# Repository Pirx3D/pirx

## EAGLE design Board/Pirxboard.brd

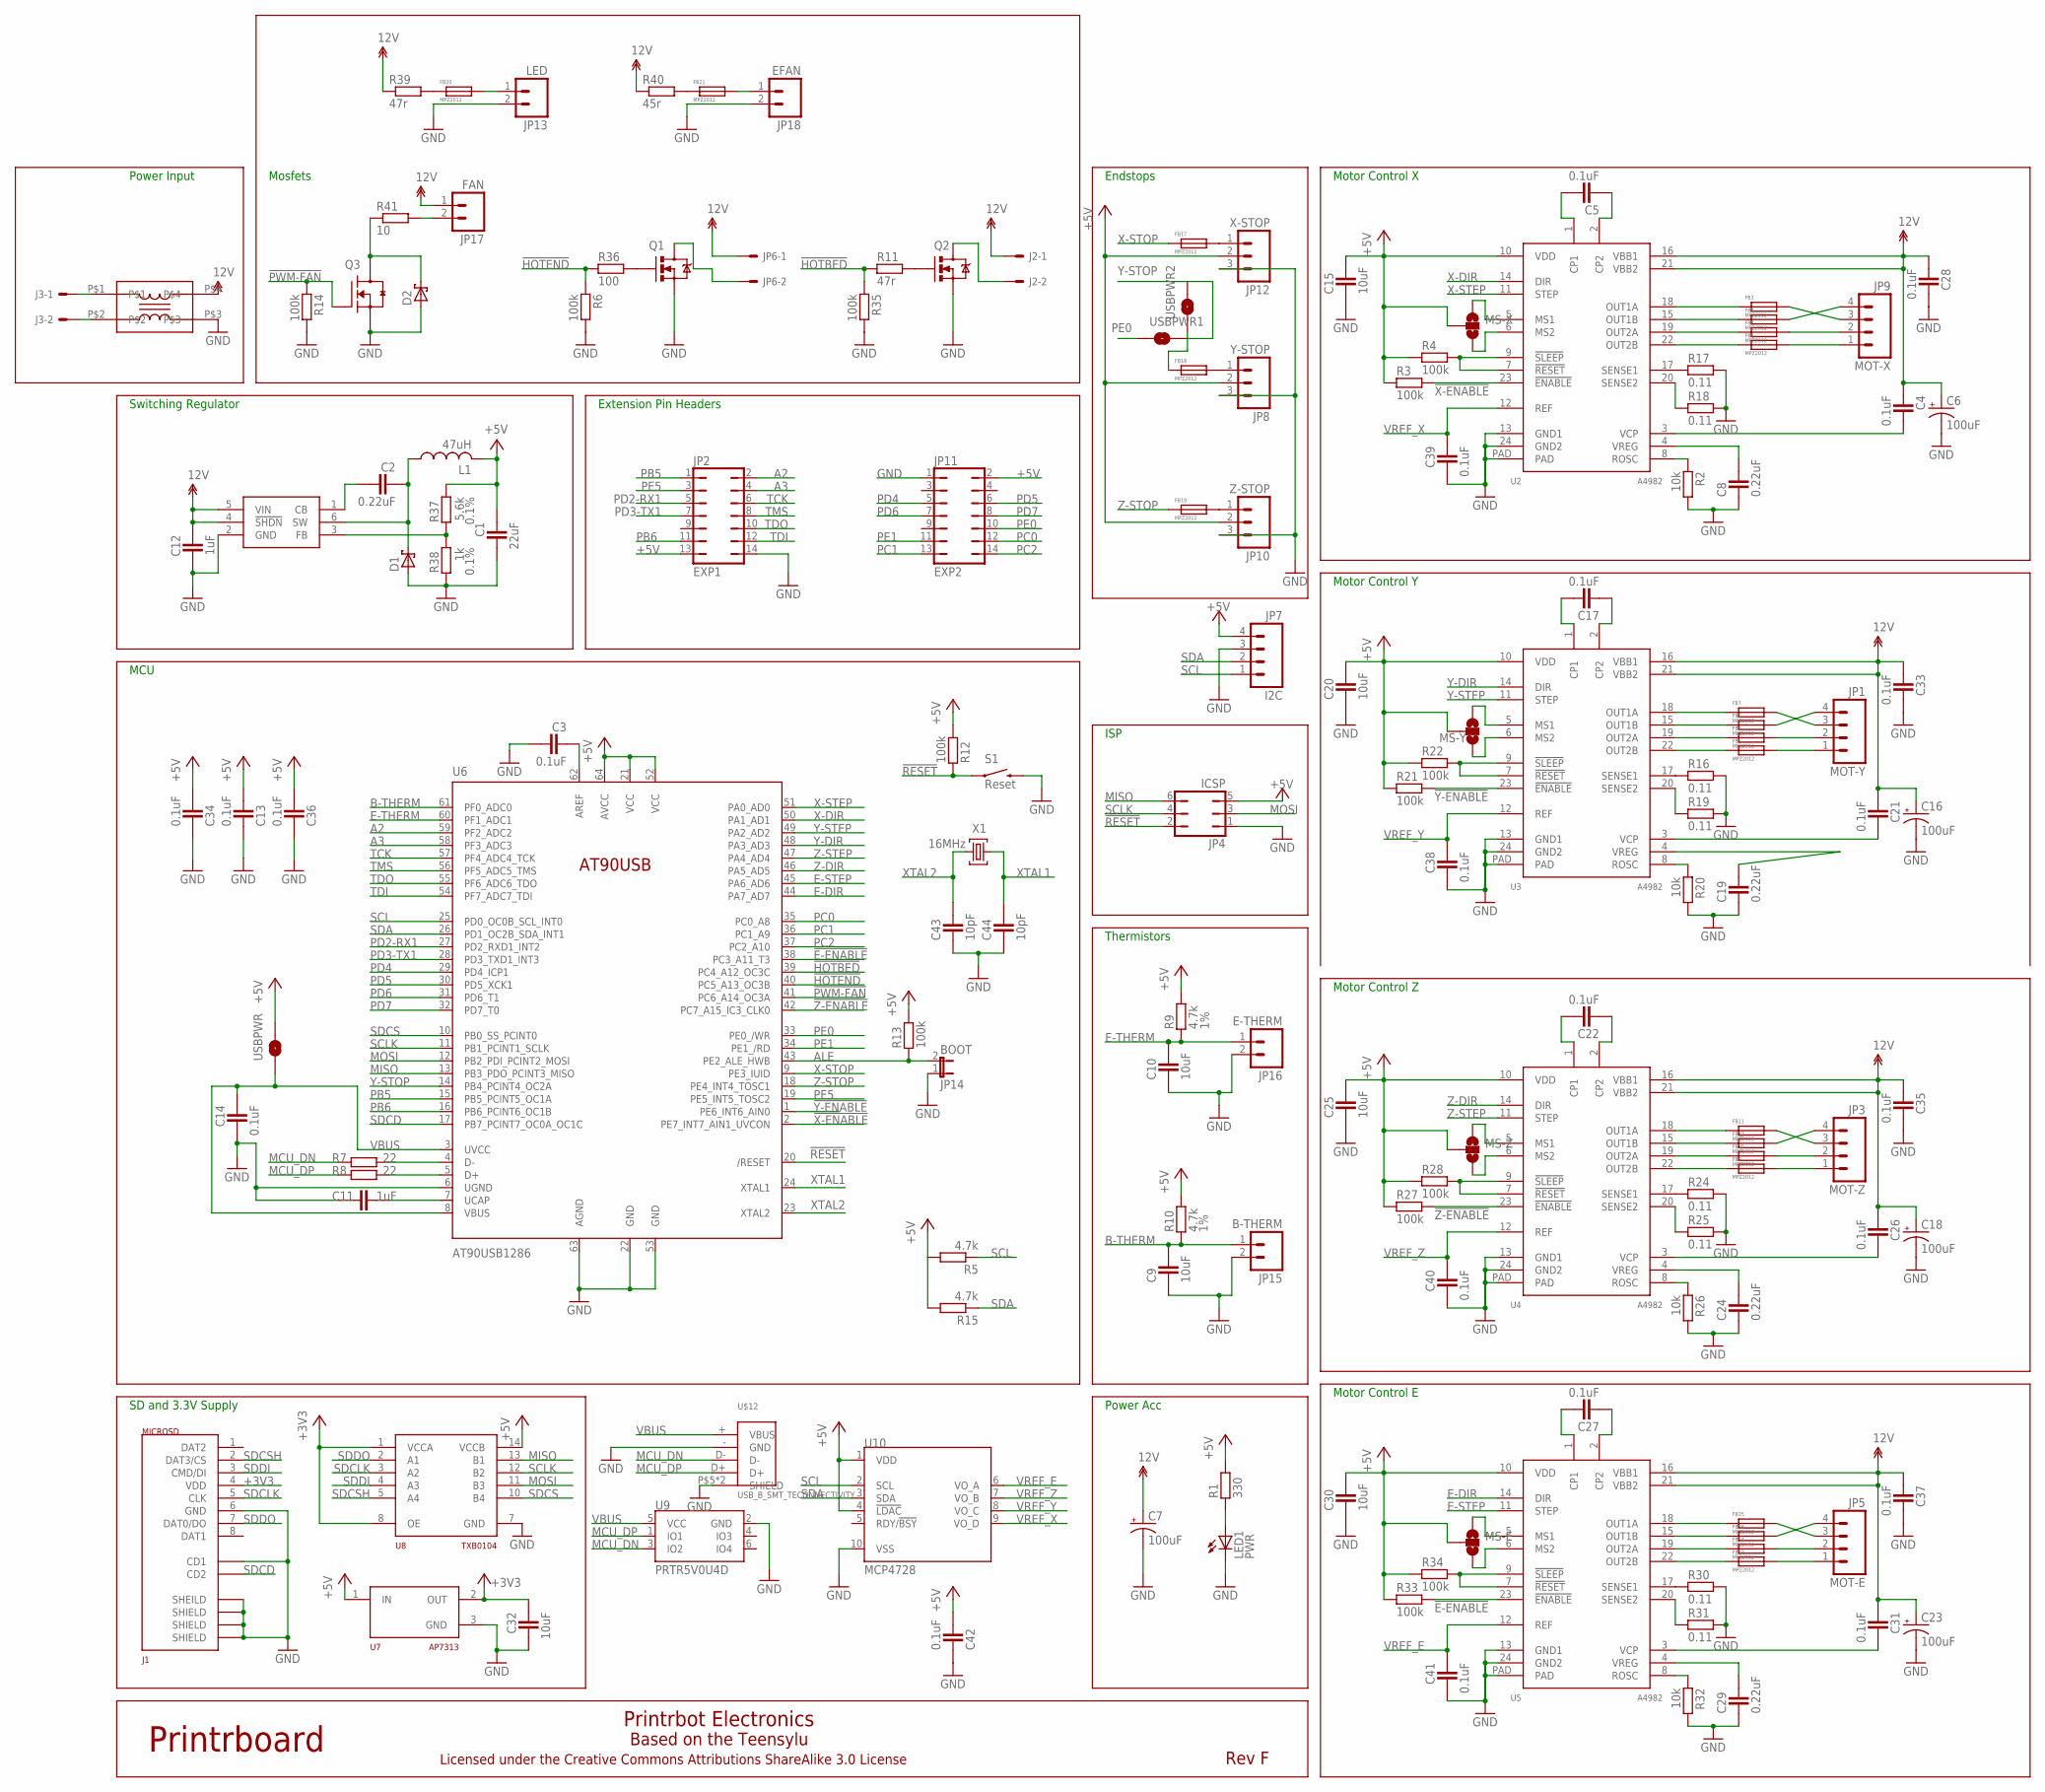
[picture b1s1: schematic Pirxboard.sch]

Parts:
C1: 22uF; CAPC2012X145AN
C2, C8, C19, C24, C29: 0.22uF; CAPC2012X145AN
C3, C4, C5, C13, C14, C17, C21, C22, C26, C27, C28, C31, C33, C34, C35, C36, C37, C38, C39, C40, C41, C42: 0.1uF; CAPC2012X145AN
C6, C7, C16, C18, C23: 100uF; PANASONIC_D
C9, C10, C15, C20, C25, C30, C32: 10uF; CAPC2012X145AN
C11, C12: 1uF; CAPC2012X145AN
C43, C44: 10pF; CAPC2012X145AN
D1, D2: SCH-DIODESMA; SMA
FB1, FB2, FB3, FB4, FB5, FB6, FB7, FB8, FB9, FB10, FB11, FB12, FB13, FB14, FB15, FB16, FB17, FB18, FB19, FB20, FB21: MPZ2012; FB2012
J1: MICROSD; AMPHENOL-MICROSD
J2, J3: PHOENIX-2POS-5MM-SCREW; PHOENIX-5MM-2POS
JP1: MOT-Y; MOLEX-1X4
JP2: EXP1; JP7Q
JP3: MOT-Z; MOLEX-1X4
JP4: ICSP; JP3Q
JP5: MOT-E; MOLEX-1X4
JP6: PHOENIX-2POS-5MM-SCREW; PHOENIX-5MM-2POS
JP7: I2C; MOLEX-1X4
JP8: Y-STOP; MOLEX-1X3
JP9: MOT-X; MOLEX-1X4
JP10: Z-STOP; MOLEX-1X3
JP11: EXP2; JP7Q
JP12: X-STOP; MOLEX-1X3
JP13: LED; 1X02
JP14: BOOT; 1X02
JP15: B-THERM; 1X02
JP16: E-THERM; 1X02
JP17: FAN; 1X02
JP18: EFAN; 1X02
L1: 47uH; SDR1006
LED1: PWR; CHIP-LED0805
MS-E: SOLDERJUMPER_2WAYCONNECTED; SJ_3_CONNECTED
MS-X: SOLDERJUMPER_2WAYCONNECTED; SJ_3_CONNECTED
MS-Y: SOLDERJUMPER_2WAYCONNECTED; SJ_3_CONNECTED
MS-Z: SOLDERJUMPER_2WAYCONNECTED; SJ_3_CONNECTED
Q1, Q2: RFP30N06LE; TO220V
Q3: RFP30N06LE; SOT95P280X135-3N
R1: 330; RESC2012X70N
R2, R20, R26, R32: 10k; RESC2012X70N
R3, R4, R6, R12, R13, R14, R21, R22, R27, R28, R33, R34, R35: 100k; RESC2012X70N
R5, R15: 4.7k; RESC2012X70N
R7, R8: 22; RESC2012X70N
R9, R10: 4.7k; RESC2012X70N; TOLERANCE 1%
R11: 47r; RESC2012X70N
R16, R17, R18, R19, R24, R25, R30, R31: 0.11; RESC2012X70N
R36: 100; RESC2012X70N
R37: 5.6k; RESC2012X70N; TOLERANCE 0.1%
R38: 1k; RESC2012X70N; TOLERANCE 0.1%
R39: 47r; R2512
R40: 45r; R2512
R41: 10; R2512
S1: Reset; TACTILE_SWITCH_TALL
U1: LM2841; TSOT6
U2, U3, U4, U5: A4982; TSSOP-24
U6: AT90USB1286; TQFP64-2
U7: AP7313; SOT23C
U8: TXB0104; TSSOP14
U9: PRTR5V0U4D; SOT23-6
U10: MCP4728; MSOP10
U$8: ACM1513-551-2PLACM1513; ACM1513
U$12: USB_B_SMT_TECONNECTIVITY; TECONECTIVITYUSBBSMT
USBPWR, USBPWR1, USBPWR2: SOLDERJUMPERNO; SJ_2S-NO
X1: 16MHz; NDK-XTAL

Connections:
12V: C4.1, C6.+, C7.+, C12.1, C16.+, C18.+, C21.1, C23.+, C26.1, C28.1, C31.1, C33.1, C35.1, C37.1, J2.P$1, JP6.P$1, JP17.1, R39.1, R40.1, U1.4 (!SHDN), U1.5 (VIN), U2.16 (VBB1), U2.21 (VBB2), U3.16 (VBB1), U3.21 (VBB2), U4.16 (VBB1), U4.21 (VBB2), U5.16 (VBB1), U5.21 (VBB2), U$8.P$4
!E-ENABLE: R33.2, U5.23 (!ENABLE), U6.38 (PC3_A11_T3)
!HOTBED: R11.1, R35.1, U6.39 (PC4_A12_OC3C)
!HOTEND: R6.1, R36.1, U6.40 (PC5_A13_OC3B)
!PWM-FAN: Q3.1 (G), R14.1, U6.41 (PC6_A14_OC3A)
!RESET: JP4.2, R12.1, S1.A2 (1), U6.20 (/RESET)
!X-ENABLE: R3.2, U2.23 (!ENABLE), U6.2 (PE7_INT7_AIN1_UVCON)
!Y-ENABLE: R21.2, U3.23 (!ENABLE), U6.1 (PE6_INT6_AIN0)
!Z-ENABLE: R27.2, U4.23 (!ENABLE), U6.42 (PC7_A15_IC3_CLK0)
+3V3: C32.1, J1.4 (VDD), U7.2 (OUT), U8.1 (VCCA), U8.8 (OE)
+5V: C1.1, C13.2, C15.2, C20.2, C25.2, C30.2, C34.2, C36.2, C42.2, JP2.13, JP4.5, JP7.4, JP8.2, JP10.2, JP11.2, JP12.2, L1.P$2 (2), MS-E.2, MS-X.2, MS-Y.2, MS-Z.2, R1.2, R3.1, R4.1, R5.2, R9.2, R10.2, R12.2, R13.2, R15.2, R21.1, R22.1, R27.1, R28.1, R33.1, R34.1, R37.1, U2.10 (VDD), U3.10 (VDD), U4.10 (VDD), U5.10 (VDD), U6.21 (VCC), U6.52 (VCC), U6.64 (AVCC), U7.1 (IN), U8.14 (VCCB), U10.1 (VDD), U10.4 (!LDAC), USBPWR.2
A2: JP2.2, U6.59 (PF2_ADC2)
A3: JP2.4, U6.58 (PF3_ADC3)
ALE: JP14.2, R13.1, U6.43 (PE2_ALE_HWB)
AREF: C3.1, U6.62 (AREF)
B-THERM: C9.2, JP15.1, R10.1, U6.61 (PF0_ADC0)
E-DIR: U5.14 (DIR), U6.44 (PA7_AD7)
E-STEP: U5.11 (STEP), U6.45 (PA6_AD6)
E-THERM: C10.2, JP16.1, R9.1, U6.60 (PF1_ADC1)
GND: C1.2, C3.2, C6.-, C7.-, C8.1, C9.1, C10.1, C11.1, C12.2, C13.1, C14.2, C15.1, C16.-, C18.-, C19.1, C20.1, C23.-, C24.1, C25.1, C28.2, C29.1, C30.1, C32.2, C33.2, C34.1, C35.2, C36.1, C37.2, C38.2, C39.2, C40.2, C41.2, C42.1, C43.1, C44.1, D1.A, D2.A, J1.6 (GND), J1.C1 (SHEILD), J1.C2 (SHIELD), J1.C3 (SHIELD), J1.C4 (SHIELD), J1.CD1, JP2.14, JP4.1, JP7.3, JP8.3, JP10.3, JP11.1, JP12.3, JP13.2, JP14.1, JP15.2, JP16.2, JP18.2, LED1.C, Q1.3 (S), Q2.3 (S), Q3.2 (S), R2.2, R6.2, R14.2, R16.2, R17.2, R18.2, R19.2, R20.2, R24.2, R25.2, R26.2, R30.2, R31.2, R32.2, R35.2, R38.2, S1.B2 (2), U1.2 (GND), U2.13 (GND1), U2.24 (GND2), U2.PAD, U3.13 (GND1), U3.24 (GND2), U3.PAD, U4.13 (GND1), U4.24 (GND2), U4.PAD, U5.13 (GND1), U5.24 (GND2), U5.PAD, U6.6 (UGND), U6.22 (GND), U6.53 (GND), U6.63 (AGND), U7.3 (GND), U8.7 (GND), U9.2 (GND), U10.10 (VSS), U$8.P$3, U$12.- (GND), U$12.P$5 (SHIELD), U$12.P$6 (SHIELD)
HOTBED-GND: J2.P$2, Q2.2 (D)
HOTEND-GND: JP6.P$2, Q1.2 (D)
MCU_DN: R7.1, U9.3 (IO2), U$12.D-
MCU_DP: R8.1, U9.1 (IO1), U$12.D+
MISO: JP4.6, U6.13 (PB3_PDO_PCINT3_MISO), U8.13 (B1)
MOSI: JP4.3, U6.12 (PB2_PDI_PCINT2_MOSI), U8.11 (B3)
unnamed: LED1.A, R1.1
unnamed: D2.C, Q3.3 (D), R41.1
unnamed: R7.2, U6.4 (D-)
unnamed: R8.2, U6.5 (D+)
unnamed: JP17.2, R41.2
unnamed: FB4.P$1 (1), U2.15 (OUT1B)
unnamed: Q2.1 (G), R11.2
unnamed: FB2.P$1 (1), U2.19 (OUT2A)
unnamed: C11.2, U6.7 (UCAP)
unnamed: FB3.P$2 (2), JP9.3
unnamed: C5.2, U2.1 (CP1)
unnamed: C5.1, U2.2 (CP2)
unnamed: R2.1, U2.8 (ROSC)
unnamed: R17.1, U2.17 (SENSE1)
unnamed: R18.1, U2.20 (SENSE2)
unnamed: C4.2, U2.3 (VCP)
unnamed: FB4.P$2 (2), JP9.4
unnamed: FB20.P$2 (2), JP13.1
unnamed: C8.2, U2.4 (VREG)
unnamed: FB1.P$1 (1), U2.22 (OUT2B)
unnamed: R4.2, U2.7 (!RESET), U2.9 (!SLEEP)
unnamed: R37.2, R38.1, U1.3 (FB)
unnamed: FB3.P$1 (1), U2.18 (OUT1A)
unnamed: FB7.P$1 (1), U3.18 (OUT1A)
unnamed: FB8.P$1 (1), U3.15 (OUT1B)
unnamed: FB8.P$2 (2), JP1.4
unnamed: MS-X.1, U2.5 (MS1)
unnamed: MS-X.3, U2.6 (MS2)
unnamed: C17.2, U3.1 (CP1)
unnamed: C17.1, U3.2 (CP2)
unnamed: FB7.P$2 (2), JP1.3
unnamed: R19.1, U3.20 (SENSE2)
unnamed: FB21.P$2 (2), JP18.1
unnamed: R20.1, U3.8 (ROSC)
unnamed: C19.2, U3.4 (VREG)
unnamed: R22.2, U3.7 (!RESET), U3.9 (!SLEEP)
unnamed: C21.2, U3.3 (VCP)
unnamed: R16.1, U3.17 (SENSE1)
unnamed: FB12.P$2 (2), JP3.4
unnamed: FB11.P$2 (2), JP3.3
unnamed: FB6.P$1 (1), U3.19 (OUT2A)
unnamed: MS-Y.1, U3.5 (MS1)
unnamed: MS-Y.3, U3.6 (MS2)
unnamed: C22.2, U4.1 (CP1)
unnamed: C22.1, U4.2 (CP2)
unnamed: R24.1, U4.17 (SENSE1)
unnamed: R25.1, U4.20 (SENSE2)
unnamed: FB21.P$1 (1), R40.2
unnamed: R26.1, U4.8 (ROSC)
unnamed: C24.2, U4.4 (VREG)
unnamed: R28.2, U4.7 (!RESET), U4.9 (!SLEEP)
unnamed: C26.2, U4.3 (VCP)
unnamed: FB5.P$1 (1), U3.22 (OUT2B)
unnamed: FB16.P$2 (2), JP5.4
unnamed: FB15.P$2 (2), JP5.3
unnamed: FB11.P$1 (1), U4.18 (OUT1A)
unnamed: MS-Z.1, U4.5 (MS1)
unnamed: MS-Z.3, U4.6 (MS2)
unnamed: C27.2, U5.1 (CP1)
unnamed: C27.1, U5.2 (CP2)
unnamed: R30.1, U5.17 (SENSE1)
unnamed: R31.1, U5.20 (SENSE2)
unnamed: FB20.P$1 (1), R39.2
unnamed: R32.1, U5.8 (ROSC)
unnamed: C29.2, U5.4 (VREG)
unnamed: R34.2, U5.7 (!RESET), U5.9 (!SLEEP)
unnamed: C31.2, U5.3 (VCP)
unnamed: FB12.P$1 (1), U4.15 (OUT1B)
unnamed: J3.P$1, U$8.P$1
unnamed: J3.P$2, U$8.P$2
unnamed: Q1.1 (G), R36.2
unnamed: MS-E.1, U5.5 (MS1)
unnamed: MS-E.3, U5.6 (MS2)
unnamed: FB2.P$2 (2), JP9.2
unnamed: C2.1, D1.C, L1.P$1 (1), U1.6 (SW)
unnamed: FB1.P$2 (2), JP9.1
unnamed: C2.2, U1.1 (CB)
unnamed: FB10.P$1 (1), U4.19 (OUT2A)
unnamed: FB9.P$1 (1), U4.22 (OUT2B)
unnamed: FB15.P$1 (1), U5.18 (OUT1A)
unnamed: FB16.P$1 (1), U5.15 (OUT1B)
unnamed: FB14.P$1 (1), U5.19 (OUT2A)
unnamed: FB13.P$1 (1), U5.22 (OUT2B)
unnamed: FB14.P$2 (2), JP5.2
unnamed: FB13.P$2 (2), JP5.1
unnamed: FB10.P$2 (2), JP3.2
unnamed: FB9.P$2 (2), JP3.1
unnamed: FB6.P$2 (2), JP1.2
unnamed: FB5.P$2 (2), JP1.1
unnamed: FB17.P$2 (2), JP12.1
unnamed: FB18.P$2 (2), JP8.1
unnamed: FB19.P$2 (2), JP10.1
PB5: JP2.1, U6.15 (PB5_PCINT5_OC1A)
PB6: JP2.11, U6.16 (PB6_PCINT6_OC1B)
PC0: JP11.12, U6.35 (PC0_A8)
PC1: JP11.13, U6.36 (PC1_A9)
PC2: JP11.14, U6.37 (PC2_A10)
PD2-RX1: JP2.5, U6.27 (PD2_RXD1_INT2)
PD3-TX1: JP2.7, U6.28 (PD3_TXD1_INT3)
PD4: JP11.5, U6.29 (PD4_ICP1)
PD5: JP11.6, U6.30 (PD5_XCK1)
PD6: JP11.7, U6.31 (PD6_T1)
PD7: JP11.8, U6.32 (PD7_T0)
PE0: JP11.10, U6.33 (PE0_/WR), USBPWR1.1
PE1: JP11.11, U6.34 (PE1_/RD)
PE5: JP2.3, U6.19 (PE5_INT5_TOSC2)
SCL: JP7.1, R5.1, U6.25 (PD0_OC0B_SCL_INT0), U10.2 (SCL)
SCLK: JP4.4, U6.11 (PB1_PCINT1_SCLK), U8.12 (B2)
SDA: JP7.2, R15.1, U6.26 (PD1_OC2B_SDA_INT1), U10.3 (SDA)
SDCD: J1.CD2, U6.17 (PB7_PCINT7_OC0A_OC1C)
SDCLK: J1.5 (CLK), U8.3 (A2)
SDCS: U6.10 (PB0_SS_PCINT0), U8.10 (B4)
SDCSH: J1.2 (DAT3/CS), U8.5 (A4)
SDDI: J1.3 (CMD/DI), U8.4 (A3)
SDDO: J1.7 (DAT0/DO), U8.2 (A1)
TCK: JP2.6, U6.57 (PF4_ADC4_TCK)
TDI: JP2.12, U6.54 (PF7_ADC7_TDI)
TDO: JP2.10, U6.55 (PF6_ADC6_TDO)
TMS: JP2.8, U6.56 (PF5_ADC5_TMS)
VBUS: C14.1, U6.3 (UVCC), U6.8 (VBUS), U9.5 (VCC), U$12.+ (VBUS), USBPWR.1
VREF_E: C41.1, U5.12 (REF), U10.6 (VO_A)
VREF_X: C39.1, U2.12 (REF), U10.9 (VO_D)
VREF_Y: C38.1, U3.12 (REF), U10.8 (VO_C)
VREF_Z: C40.1, U4.12 (REF), U10.7 (VO_B)
X-DIR: U2.14 (DIR), U6.50 (PA1_AD1)
X-STEP: U2.11 (STEP), U6.51 (PA0_AD0)
X-STOP: FB17.P$1 (1), U6.9 (PE3_IUID)
XTAL1: C44.2, U6.24 (XTAL1), X1.P$1 (1)
XTAL2: C43.2, U6.23 (XTAL2), X1.P$2 (2)
Y-DIR: U3.14 (DIR), U6.48 (PA3_AD3)
Y-STEP: U3.11 (STEP), U6.49 (PA2_AD2)
Y-STOP: FB18.P$1 (1), U6.14 (PB4_PCINT4_OC2A), USBPWR1.2, USBPWR2.1, USBPWR2.2
Z-DIR: U4.14 (DIR), U6.46 (PA5_AD5)
Z-STEP: U4.11 (STEP), U6.47 (PA4_AD4)
Z-STOP: FB19.P$1 (1), U6.18 (PE4_INT4_TOSC1)

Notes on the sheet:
Motor Control X
Motor Control Y
Motor Control Z
Motor Control E
ISP
Thermistors
Endstops
Mosfets
Power Acc
Printrboard
Rev F
Printrbot Electronics
Licensed under the Creative Commons Attributions ShareAlike 3.0 License
Extension Pin Headers
Switching Regulator
Based on the Teensylu
SD and 3.3V Supply
Power Input
MCU

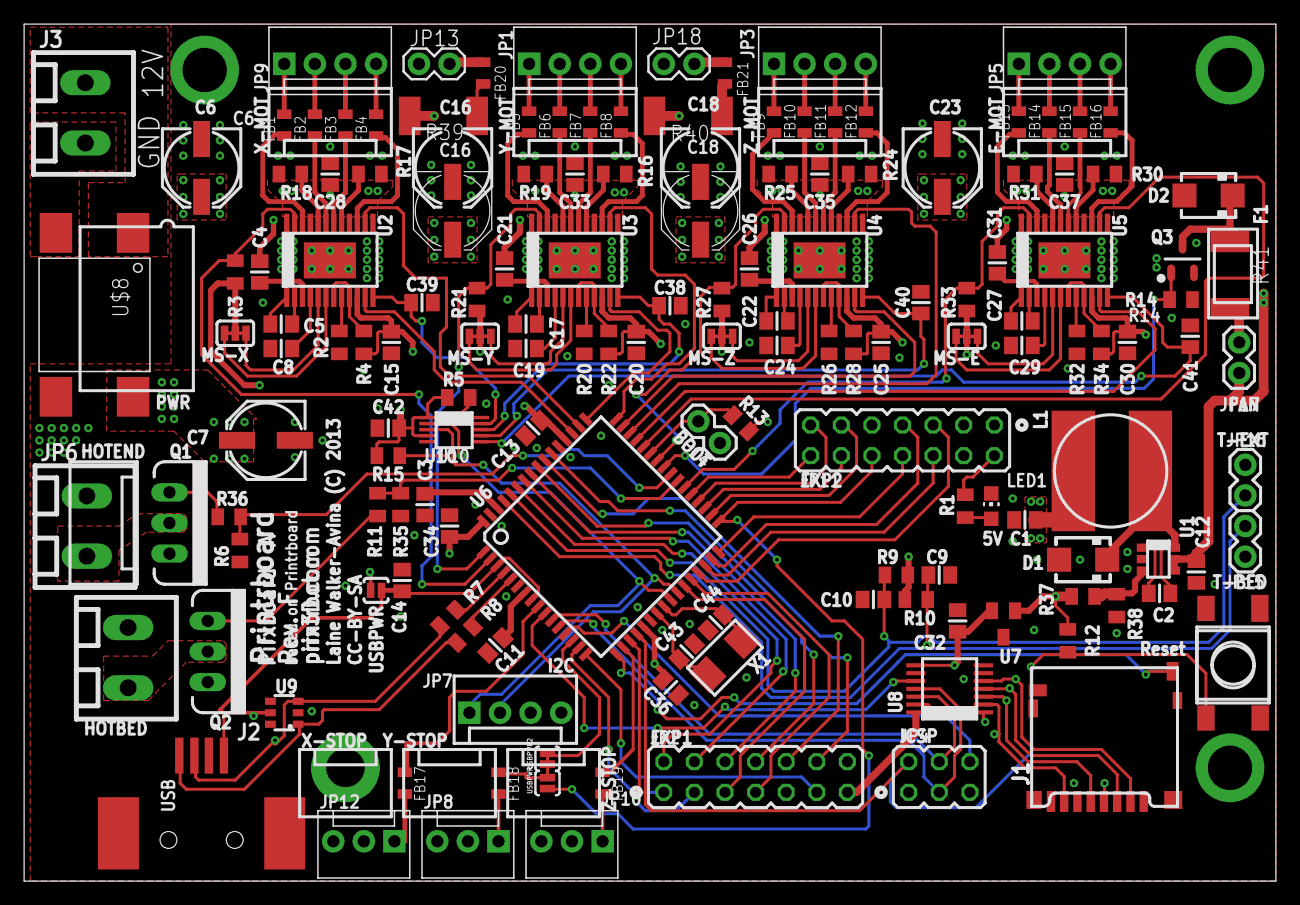
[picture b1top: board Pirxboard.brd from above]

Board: 4 copper layers, 103.9 x 71.1 mm, 153 parts (0 on the bottom side), 161 nets.

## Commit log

2015-02-02 :tada: Added .gitattributes & .gitignore files
2015-02-02 Pirx 3d printer full source
2015-03-04 Added pdf files with drawings of machined parts
2015-03-13 Added STP file with the whole thing

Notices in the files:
Board/Pirxboard.brd:
Laine Walker-Avina (C) 2013
CC-BY-SA
